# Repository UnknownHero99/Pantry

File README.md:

# Pantry

Self-hosted home inventory: pantry, fridge, freezer, garage, anything with a shelf.
Scan things **in** when you put them away and **out** when you use them, and always
know what you have.

- **Store-bought:** scan the product's own barcode (EAN/UPC). Name, brand and photo
  come from Open Food Facts, or for cleaners, toilet paper and toiletries from its
  sister databases Open Products Facts and Open Beauty Facts. Slovenian names come
  from [Veš, kaj ješ?](https://veskajjes.si) (ZPS), which is asked at the same time
  and also covers products Open Food Facts doesn't know. Packs of the same
  product are counted together.
- **Home-made** (harvest, bulk meat, meal prep): *Pack & label* prints one QR label per
  package on a Bluetooth cat printer. Each package keeps its own weight, packed date
  and use-by date, and scanning it OUT removes that exact package.
- **Wall scanner:** ESP32-P4 4.3" touchscreen (Guition) + GM67 barcode module, ESPHome firmware
  (`esphome/`). TAKE OUT / PUT AWAY modes, product photo, count before → after,
  −/+ for multiples, QR to name unknown barcodes, offline queue, ambient night clock.
- **Phone PWA:** camera scanning, inventory, shopping list, inbox for unknown barcodes,
  history with undo. Pages still open offline, and offline scans are queued and replayed.
- **Home Assistant:** shopping list mirrored to a to-do list; `/api/summary` for sensors.

Stack: SvelteKit (adapter-node) + SQLite (`node:sqlite`, no native deps), one container.

## Screenshots

The wall scanner: waiting for a scan, a product taken out, a home-made package taken out.

The phone app: Pantry stock, the Garage, one box, the shopping list, packing and labelling home-made food.

## Run

```bash
cp .env.example .env     # set ORIGIN, optionally HA_*
docker compose pull && docker compose up -d
docker logs pantry       # the one-time setup code
```

Open the app, enter the setup code from the log and create the admin account. Then, in
**More → Users & devices**, add the rest of the household and make a device token for the
wall scanner (and one for Home Assistant).

Every push to `master` builds `ghcr.io/unknownhero99/pantry:latest` (amd64 + arm64) in GitHub Actions. To run your own checkout instead, use `docker compose up -d --build`.

Data (SQLite DB + cached product photos) lives in `./data` → `/data` in the container.

Dev: `npm install && npm run dev` (port 5190, data in `./data`).

### Environment

| Var | |
|---|---|
| `ORIGIN` | Public HTTPS URL behind your reverse proxy, e.g. `https://pantry.example.com`. SvelteKit form posts check it. |
| `DATA_DIR` | Defaults to `/data` in the image. |
| `TZ` | Time zone for History, e.g. `Europe/Ljubljana` (the default in `docker-compose.yml`). |
| `HA_URL`, `HA_TOKEN`, `HA_TODO_ENTITY` | Optional grocery-list sync, e.g. `http://192.168.10.10:20810`, a long-lived token, `todo.shopping_list`. |
| `HA_TODO_ENTITY_GARAGE` | Optional: the garage shopping list into its own HA to-do list, e.g. `todo.hardware_store`. |
| `HA_NOTIFY` | Optional: "Lent to…" reminders as phone notifications, e.g. `notify.mobile_app_pixel_8`. |
| `TRUSTED_PROXIES` | Optional: comma-separated addresses of your reverse proxy. Only they may set `X-Forwarded-For` / `-Proto` / `-Host`. Unset, any private or loopback address is trusted (a proxy on the LAN or in Docker). |

### Reverse proxy

The phone needs **HTTPS** for the camera, PWA install and Web Bluetooth. Proxy to port
5190. `/api/events` is a server-sent-events stream, so turn off response buffering for
it (nginx: `proxy_buffering off;`; the app also sends `X-Accel-Buffering: no`).

The wall scanner talks plain HTTP straight to `http://<nas>:5190`, not through the proxy.

The proxy must pass `X-Forwarded-For` and `X-Forwarded-Proto` (Caddy, Traefik and Nginx Proxy
Manager do by default; plain nginx needs `proxy_set_header X-Forwarded-For
$proxy_add_x_forwarded_for;` and `proxy_set_header X-Forwarded-Proto $scheme;`). Pantry uses them
to rate-limit sign-in per client and to mark the session cookie `Secure`. HSTS belongs on the proxy.

## Sign-in and security

Everything except the sign-in page needs an account; nothing is readable without one.

- **People** sign in with a username and password (6+ characters, scrypt-hashed). The browser
  gets a random session cookie (`HttpOnly`, `SameSite=Lax`, `Secure` over HTTPS) that lasts 30
  days from the last visit, so phones stay signed in. The database stores only a hash of it.
  **More → Account** changes your password (which signs out your other devices), lists where
  you're signed in and signs any of them out.
- **Admins** also get **More → Users & devices**: add people, set a new password for someone,
  make them admin, remove them. There's always at least one admin.
- **Devices** (the wall scanner, Home Assistant) use a token from Users & devices, sent as
  `Authorization: Bearer pnt_…`. A token opens `/api/*` and `/img/*`, never the pages, is shown
  once, stored hashed, and can be revoked there at any time.
- **First run:** with no accounts, every page goes to `/setup`, which asks for a one-time code
  printed in the server log, so whoever reaches a fresh install first can't claim it.
- **Brute force:** after 10 failed sign-ins from one address, or 20 for one username, in 15
  minutes, sign-in is refused for the rest of that window. Failures are logged with the
  client's address.
- **Cross-site requests:** every POST from a browser must come from this site (its `Origin`
  is checked against the request's host, `ORIGIN`, or the proxy's `X-Forwarded-Host`). Pages
  send a Content-Security-Policy (scripts only from the app), `X-Frame-Options: DENY`,
  `nosniff` and `Referrer-Policy: same-origin`.

Locked out? Remove the users and Pantry asks for setup again (stock is untouched):

```bash
docker exec pantry node -e "new (require('node:sqlite').DatabaseSync)('/data/pantry.db').exec('DELETE FROM users')"
docker restart pantry && docker logs pantry
```

## Spaces: Pantry, Kitchen, Garage

Storage is a small tree: **spaces** › **places** › **boxes**.

| Space | Places (at first) | Lists |
|---|---|---|
| **Pantry**, the home space | Shelves, Freezer | Groceries, *Use soon*. The wall scanner files here. |
| **Kitchen** | Fridge, Freezer | Groceries, *Use soon* (same lists as Pantry) |
| **Garage** | Unsorted (+ your shelves) | its own Garage shopping list |

- The **Stock** tab opens on Pantry; tap the title (*Pantry ▾*) to switch space.
  Search always looks **everywhere** and answers with the path,
  e.g. *Garage › Shelf A › A·1 Power tools*.
- Add spaces and places in **Settings → Spaces and places**. A space shops into either
  Groceries or the Garage list.
- **Boxes:** on a shelf's page, *+ New numbered boxes* makes A·1, A·2… and prints their
  labels on the P15 (QR `PNTRY:B:…`). Scanning a box label on the phone opens the box;
  *Move box* moves everything inside with it.
- **Sorting the garage:** open a box, *+ Put in*: snap a photo, name it, *Tool / Spare part
  / Other*, what a spare part **fits**, *Just 1* or *Count them*. *Save, next thing*.
  Not sure where something goes? Put it in *Unsorted* and move it later.
- **Counted** things (bulbs, filters, screws) have a quantity and a minimum, like food.
  **Located** things (a drill) only have a place: *Took it* / *Put back*, *Move…*,
  and *Lent to…* with a reminder (7 / 14 / 30 days) through Home Assistant.
- Migrating from before spaces: the old Pantry becomes *Pantry › Shelves*, Freezer
  *Pantry › Freezer*, Fridge *Kitchen › Fridge*; nothing else changes.

See `docs/storage-design.md` for the reasoning.

## Using it

The phone app looks and talks like the wall: dark, TAKE OUT / PUT AWAY, the same result
card. Tabs: Stock · Shop · **Scan** (the big middle button) · Pack · More.

| Screen | |
|---|---|
| **Stock** | Tiles for *to buy*, *use soon*, *to name*; search; filter by place; tap a count for −/+ |
| **Shop** | Groceries and Garage lists: below *min stock*, with photos. Ticks ("in the trolley") stay on your phone; *Put away* opens Scan in put-away mode |
| **Scan** | Camera (+ torch, + type a code), TAKE OUT / PUT AWAY (falls back after 2 min, like the wall), result card with −/+, undo, fix count, the trip list |
| **Pack** | Home-made goods: recent products as chips, packs × amount, where, use-by chips, live label preview → print |
| **Product** | Count per place, packages, details. An unknown barcode (the wall's QR code lands here) opens as a quick *name it* form |
| **More → Inbox** | Barcodes neither Open Food Facts nor Veš kaj ješ knew |
| **More → History** | By day, filter wall / phones / count issues, undo any of them |
| **More → Settings** | Locations, printer darkness + test print |

Set **Min stock** on a product to have it appear on the shopping list.
**Keeps (days)** pre-fills use-by when packing. It's learned from the first pack if blank.

### Label printers

Printing happens **from the phone over Web Bluetooth**: Chrome on Android, over HTTPS.
On the first print, Chrome lists nearby Bluetooth devices; pick the printer. The app
recognises which kind it is and draws the label for it. Choose the kind in **Settings** so
previews match before you've connected. Close the printer's own app first: these printers
take one connection at a time.

| | **P15** label maker (Marklife / Pristar P15, P12, L13) | **C15** "cat" printer (Fun Print) |
|---|---|---|
| Labels | 12–15 mm die-cut labels, 30 / 40 / 50 mm long (set in Settings) | 57 mm thermal sticker roll |
| Layout | QR across the full 12 mm height, name / amount / dates beside it | QR left, larger text right |
| Driver | `src/lib/p15printer.js`: service `0xFF00`, ESC/POS raster (`GS v 0`) in a `10 FF …` job | `src/lib/catprinter.js`: the `51 78 …` protocol (MX/GB models) |
| Darkness | fixed | slider in Settings |

The P15 job format follows what the [LaBLEr](https://github.com/toolicious/labler) project
verified on a P15 (our bytes match its reference job exactly). If a printer isn't
recognised, the error lists the Bluetooth services it does offer. Stick labels on dry bags
*before* freezing.

Labels encode `PNTRY:I:000123`. The wall scanner and phone camera both read them.

## Wall scanner (`esphome/`)

### Parts

Everything is off the shelf; no custom board needed. Prices are delivered to Slovenia
with VAT and the EU's per-item import charges (about €6.10 an item from China, November
2026). [hardware/shopping-list.md](hardware/shopping-list.md) has the listings and says
which parts to buy locally instead, because the charge is several times their price.

| | |
|---|---|
| Guition **JC4880P443C** (ESP32-P4 + ESP32-C6 for Wi-Fi, 4.3" 480×800 IPS used in landscape, GT911 capacitive touch) | ~€38 |
| **GROW GM67** barcode module (1D + 2D, red aiming light, 5 V, TTL UART; comes with its cables). The [enclosure](hardware/enclosure) is made for it; a GM65 or the SparkFun breakout works with the same firmware. | ~€25 |
| **Speaker**, 8 Ω 1–2 W, round 28 mm × 5 mm, with a 1.25 mm 2-pin plug on a lead of 15 cm or more: it plugs into the board's own amplifier | ~€10 |
| **WS2812B LED module**, a single LED (DIN, VCC, GND) | ~€1 |
| Three female Dupont wires, a **right-angle** USB-C cable and a 5 V 2 A supply | ~€15 |
| [3D-printed case](hardware/enclosure) (or any wall box) | |

The speaker and LED are optional. Without the speaker, the GM67's own beep confirms each
read (leave its silent mode off), and the firmware can stay as it is: the sounds just play
to nothing. Without both, drop the `feedback` package and the speaker section from
`pantry-scanner.yaml`.

### Wiring

| Guition | Goes to |
|---|---|
| The 1.25 mm 4-pin socket marked **5V, IO26, IO27, GND**: `5V` | GM67 UART pin 1 `5V` |
| `IO26` (the board's RX) | GM67 pin 2 `TX` |
| `IO27` (the board's TX) | GM67 pin 3 `RX` |
| `GND` | GM67 pin 4 `GND` |
| **Speaker socket** (1.25 mm 2-pin, on the board's top edge) | speaker |
| **JP1** (2×13 header) pins **2, 4, 6**: 3.3 V, GND, GPIO33 | LED VCC, GND, DIN |

Pin for pin, so the GM67's own 4-pin UART cable plugs straight in. The GM67's UART socket
is the one marked UART, next to the USB one. Not **CN2 "UART0"**: on this board it's
GPIO21/GPIO38, and a GM67 on it never got through.

The LED takes three neighbouring header pins, so it's one 3-pin Dupont plug and no
splicing. It runs on 3.3 V so its data input sees a full-level signal; WS2812B LEDs are
rated from 3.5 V but work at 3.3 V. The speaker is driven by the board's ES8311 audio chip
and amplifier (enabled on GPIO11); the scan sounds are the same tunes a buzzer would play.

Flashing and logs go over the USB-C marked **full speed** (the ESP32-P4's USB
Serial/JTAG), so the scanner can stay plugged in.

**Other boards.** [esphome/pantry-sunton.yaml](esphome/pantry-sunton.yaml) is the same
thing on the Sunton **ESP32-8048S043C** (ESP32-S3, ~€52 delivered), with its wiring in the
file's header. Two optional custom boards, neither needed:
[hardware/scanner-carrier](hardware/scanner-carrier) sits behind the Sunton with sockets for
the scanner, a buzzer and a status LED; [hardware/mainboard](hardware/mainboard) replaces it
with one 4-layer board for the bare panel ([esphome/pantry-mainboard.yaml](esphome/pantry-mainboard.yaml)).

### Scanner module setup

Using the configuration barcodes in the scanner's manual (the
[GM67 manual](https://makerselectronics.com/wp-content/uploads/2026/07/GM67-Barcode-Reader-Module-User-Manual-V1.3.pdf)):
**serial (UART) output, 9600 baud, induction/continuous mode, add CR suffix**, and make
sure QR codes are enabled. The GM67 also beeps by itself on every read; its **silent mode**
leaves the beeping to the speaker, which sounds different for each result. With no
speaker, leave silent mode off.
(Or keep its baud rate and change `scanner_baud` in `pantry-scanner.yaml`.)

### Flash

```bash
cd esphome
cp secrets.example.yaml secrets.yaml   # Wi-Fi, API key: openssl rand -base64 32 (OTA uses it too)
# edit substitutions at the top of pantry-scanner.yaml: server URL, location name
docker run --rm -it -v "$PWD":/config --device /dev/ttyACM0 esphome/esphome run pantry-scanner.yaml
```

The first flash prints the chip's revision (`Chip is ESP32-P4 (revision v…)`). Below
v3.0 it's an early chip: set `engineering_sample: "true"` in `pantry-scanner.yaml` and
flash again. After that, update over Wi-Fi.

Or use the ESPHome dashboard in Home Assistant: copy `pantry-scanner.yaml`,
`pantry-ui.yaml` (the screens), `pantry-feedback.yaml` (LED and scan sounds) and `pantry_ui.h`
into its config folder. The board shows up in HA with a backlight light
and a "Last scan" sensor, and takes its clock from HA, so it needs no internet.

**Wi-Fi co-processor.** The P4 has no radio; Wi-Fi is the ESP32-C6 beside it. These boards
ship with an older C6 firmware than ESPHome expects, which can drop Wi-Fi now and then.
Once the scanner is in HA, install the **Wi-Fi co-processor** update it offers (ESPHome's
build, downloaded by the scanner itself).

Make a device token in the app (**More → Users & devices → New token**, e.g. "Wall
scanner") and put it in `secrets.yaml` as `pantry_token`; the scanner sends it with every
request. Without it, or after it's revoked, the server answers 401 and the scanner can't
scan, so make the token before flashing.

Set `ORIGIN` on the server: the unknown-barcode screen shows a QR code of
`<ORIGIN>/product/<id>`, which opens the product on your phone to name it.

The config is validated and compiles against ESPHome 2026.10 (RAM 16%, flash 24%), but
hasn't run on a board yet. The display and Wi-Fi settings are ESPHome's own for this board
(`model: JC4880P443`, ESP-Hosted over SDIO) and the pins come from its schematic notes.
If the picture is upside down, set `rotation: "270"`. Touch is polled, because the
sources disagree on its reset and interrupt pins.

### Try it without the hardware

`pantry-sim.yaml` runs the same screens in an 800×480 window on a Linux desktop (X11).
The mouse is the touchscreen, and a small script stands in for the barcode module.
It talks to the app on `http://127.0.0.1:5190`, so start that first (`npm run dev`).

Put a device token from the app in `token:` at the top of `pantry-sim.yaml` first.

```bash
esphome/sim/run.sh                   # builds a Docker image with SDL, compiles, opens the window
esphome/sim/scan 3017620422003       # "scan" a barcode (Nutella); PNTRY:I:000001 for a label
```

The first build takes a few minutes. Set `ORIGIN` in `.env` to see the QR code on
the unknown-barcode screen. The backlight does nothing in the window, so the night screen
shows at full brightness.

**Network:** if the scanner lives on the IoT VLAN, the router needs an allow rule from
it to the NAS on TCP 5190.

### On the wall

The screen has a status bar on top (clock, or a blue "PUTTING AWAY" band), a card in the
middle, and a fixed bottom bar: **TAKE OUT | PUT AWAY** and **UNDO**.

- **Take out** is the default. Scan anything you take: the card shows the photo,
  **3 → 2 left**, and goes back to the home screen (what to buy, what to use soon,
  items to name) after 8 seconds. Took two? Tap **+**.
- **Put away** before unpacking shopping. The top bar turns blue and counts down; after
  2 minutes without a scan it falls back to take out. Each scan shows **2 → 3** and lands
  in the *This trip* list. Bought six of the same? Scan one, tap **+** five times.
- **First time a barcode is seen:** "Looking it up…" while the server asks Open Food
  Facts in the background. If it isn't found, the screen shows a **QR code**: point
  your phone at it to name the product right away, or do it later from the inbox.
- **Took the last one:** an amber banner says so, and whether it's on the shopping list
  (set *Min stock* on the product for that).
- **Home-made package:** packed date, use-by, what's left, and a hint if an older pack
  should be used first.
- **Nothing in stock** (counts drifted): *It was there, fix count* records the one the
  app didn't know about.
- **UNDO** opens a list of this scanner's last 5 scans from the past day, newest on top.
  Tap the one to reverse (any −/+ on it is reversed too); **CLOSE** or 20 s without a
  tap closes the list.
- **Server unreachable:** keep scanning. Scans wait on the scanner and are sent when the
  server is back (kept in RAM, so a power cut loses them).
- After 5 minutes without a touch or scan it shows a dim clock with what to buy and use
  soon; a touch or scan wakes it.

## Home Assistant

Shopping list: set the `HA_*` variables. The app adds and removes only the items it put
there, so items you add by hand are left alone.

Sensors from `/api/summary`, with a device token (Users & devices → New token, e.g. "Home
Assistant") in HA's `secrets.yaml` as `pantry_auth: "Bearer pnt_…"`:

```yaml
rest:
  - resource: http://192.168.10.10:5190/api/summary
    headers:
      Authorization: !secret pantry_auth
    scan_interval: 300
    sensor:
      - name: Pantry low stock
        value_template: "{{ value_json.low_count }}"
        json_attributes: [low]
      - name: Pantry use soon
        value_template: "{{ value_json.expiring_count }}"
        json_attributes: [expiring]
      - name: Pantry inbox
        value_template: "{{ value_json.inbox_count }}"
```

## API

Every call needs either a signed-in browser session or `Authorization: Bearer <device token>`;
without one the answer is `401`.

| | |
|---|---|
| `POST /api/scan` `{code, mode: "in"\|"out", device?, location?, default_location?, async_lookup?}` — `location` forces a place, `default_location` only applies to products without a usual place, `async_lookup` answers at once and looks a new barcode up in the background | → `{status: ok\|lookup\|unknown\|empty\|error, title, detail, count, prev, units, meta, image, qr, last_one, pkg, use_by, older, product_id, event_id, …}` (see `scanReply` in `inventory.js`) |
| `GET /api/scan/:event` | The same reply for an earlier scan; the wall polls it while `status` is `lookup` |
| `POST /api/scan/:event/adjust` `{by: 1\|-1}` | One more or one fewer of that scan ("bought six") |
| `POST /api/scan/:event/fix` | For a nothing-in-stock OUT: record that there was one |
| `GET /api/scan/recent?device=wall` | That device's last 5 scans from the past day that can still be undone (the wall's UNDO list) |
| `POST /api/undo` `{event_id?}` | Undo that event, or the latest one |
| `GET /api/summary` | `{low_count, low[], expiring_count, expiring[], soon[{name, n, days}], inbox_count, garage_low_count, lent_out, overdue[]}` (`low` is groceries) |
| `GET /api/labels?ids=1,2` | Label data for reprinting |
| `GET /api/events` | SSE stream: `change` whenever stock moves |

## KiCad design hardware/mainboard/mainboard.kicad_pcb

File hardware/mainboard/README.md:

# Wall scanner mainboard

Everything for the wall scanner on one board: it replaces the Sunton ESP32-8048S043C.
A 100 × 60 mm, 4-layer board that sits behind a bare 4.3" 800×480 RGB panel; every part
is on the back, so JLCPCB assembles one side only. Optional: an off-the-shelf display
board plus modules does the same job (see the [main README](../../README.md#wall-scanner-esphome)).
Goes into the [printable enclosure](../enclosure) built with `board = "mainboard"`
(`stl/mainboard-*.stl`).

- **ESP32-S3-WROOM-1-N16R8** (16 MB flash, 8 MB PSRAM), antenna over the top edge.
- **USB-C** is the ESP32-S3's native USB: power, flashing and logs. ESD protected (USBLC6),
  works with USB-C chargers (5.1 k CC pull-downs).
- **3.3 V**: SY8089 buck, 2 A.
- **Display**: 40-pin 0.5 mm ribbon (Hirose FH12, bottom contact), 16-bit RGB like the
  Sunton. The ESP32-S3 can put these signals on any GPIO, so they're assigned in the order
  they meet the module's edge seen from the connector: the 20 display lines reach it
  without crossing (with the Sunton's pin order they'd cross about 90 times).
  **Backlight**: TPS61169 constant-current boost (about 20 mA, 37.5 V limit), PWM from IO5.
- **Touch**: GT911 on a 6-pin 1.0 mm ribbon; IO39 SDA, IO40 SCL, IO41 INT, IO42 RST.
- **Scanner** on UART0 (IO43/44), which is free because flashing goes over USB:
  - **J4**: SparkFun 2D Barcode Scanner Breakout (DE2120, red aiming line), 3.3 V, on a
    1×6 socket. In the [enclosure](../enclosure) it sits in the bevelled mouth under the
    screen and connects with a short 6-wire Dupont cable; without the enclosure a
    right-angle header plugs it straight in.
  - **J5**: any 5 V UART module (GM65, GM805, GM861…) on a 4-pin 1.25 mm cable instead.
  Fit only one.
- **Buzzer** MLT-8530 (IO2) and a **status LED**: side-view SK6812 on the bottom edge
  shining down (IO1, level-shifted to 5 V).
- **RESET** and **BOOT** buttons (rarely needed: USB flashing doesn't need them).

## Files

| | |
|---|---|
| `fab/mainboard-gerbers.zip` | Gerbers + drill files for JLCPCB: **4 layers**, 1.6 mm |
| `fab/bom-jlcpcb.csv`, `fab/cpl-jlcpcb.csv` | Parts and placement for JLCPCB assembly (LCSC numbers, in stock Oct 2026) |
| `fab/mainboard-schematic.pdf` | Schematic |
| `fab/mainboard.step` | 3D model |
| `mainboard.kicad_*` | KiCad 10 project |

## Ordering (JLCPCB)

1. Upload the Gerber zip, choose **4 layers** (the inner two are a ground and a 3.3 V plane).
2. PCB Assembly, top side, upload the BOM and CPL.
3. Check the placement preview, especially U2/U4 (SOT-23-5), U5 (SC-70-5), the two ribbon
   connectors, D3 (side LED, light toward the bottom edge) and LS1 (`+` top left).
4. J4 (1×6 socket) is through-hole: let JLCPCB fit it or solder it.

## Panel

Any 4.3" 800×480 RGB TFT with the common 40-pin pinout (LED−, LED+, GND, VDD, R0–R7,
G0–G7, B0–B7, GND, DCLK, DISP, HSYNC, VSYNC, DE, NC, GND, 4 × resistive touch) and a
GT911 capacitive touch on a separate 6-pin 1.0 mm ribbon (GND, SDA, SCL, RST, INT, VDD):
the panel the Sunton boards use. Both ribbons wrap around the board's bottom edge into
the connectors on the back.

## Firmware

[esphome/pantry-mainboard.yaml](../../esphome/pantry-mainboard.yaml): the same screens
(`pantry-ui.yaml`) and the buzzer / LED package (`pantry-feedback.yaml`) as the
Sunton build with the carrier, on this board's pins (the display block lists this board's
RGB GPIOs; the panel timing is unchanged). Flash it over USB-C the first time, over Wi-Fi
after that.

## Rebuilding

Everything comes from [tools/design.py](tools/design.py):

```bash
hardware/mainboard/tools/build.sh
```

Same steps as the [scanner carrier](../scanner-carrier#rebuilding), with a bigger router:
the USB-C escape (a fixed pattern in `design.py`: D+ joins on top, D- through two vias)
and the USB nets first, then a via for every ground and 3.3 V pad into the inner planes,
then everything else by negotiated congestion (PathFinder): nets may overlap at first, at
a price that rises each round, until none do. The strips behind the ribbon connectors are
left to the ground pour, which picks up their fine-pitch ground pins. About 10 minutes.

## Not verified yet

Nothing has been built. KiCad's checks are clean (see the build log), but:

- **The panel ribbon's contact side and pin 1 end** are the part most likely to be wrong for
  a given panel. Both connectors are bottom-contact (the ribbon's contacts face the board
  after it wraps around the edge) and have **pin 1 at the left end seen from the back of
  the board** (the right end seen from the front). Check your panel's drawing: its ribbon
  must arrive that way round, or the connectors need turning in `tools/design.py`.
- **Backlight current**: R13 = 10 Ω gives about 20 mA. Some panels want 40 mA (two strings):
  then use 5.1 Ω.
- The side LED's footprint is drawn from its datasheet (KiCad doesn't have it).

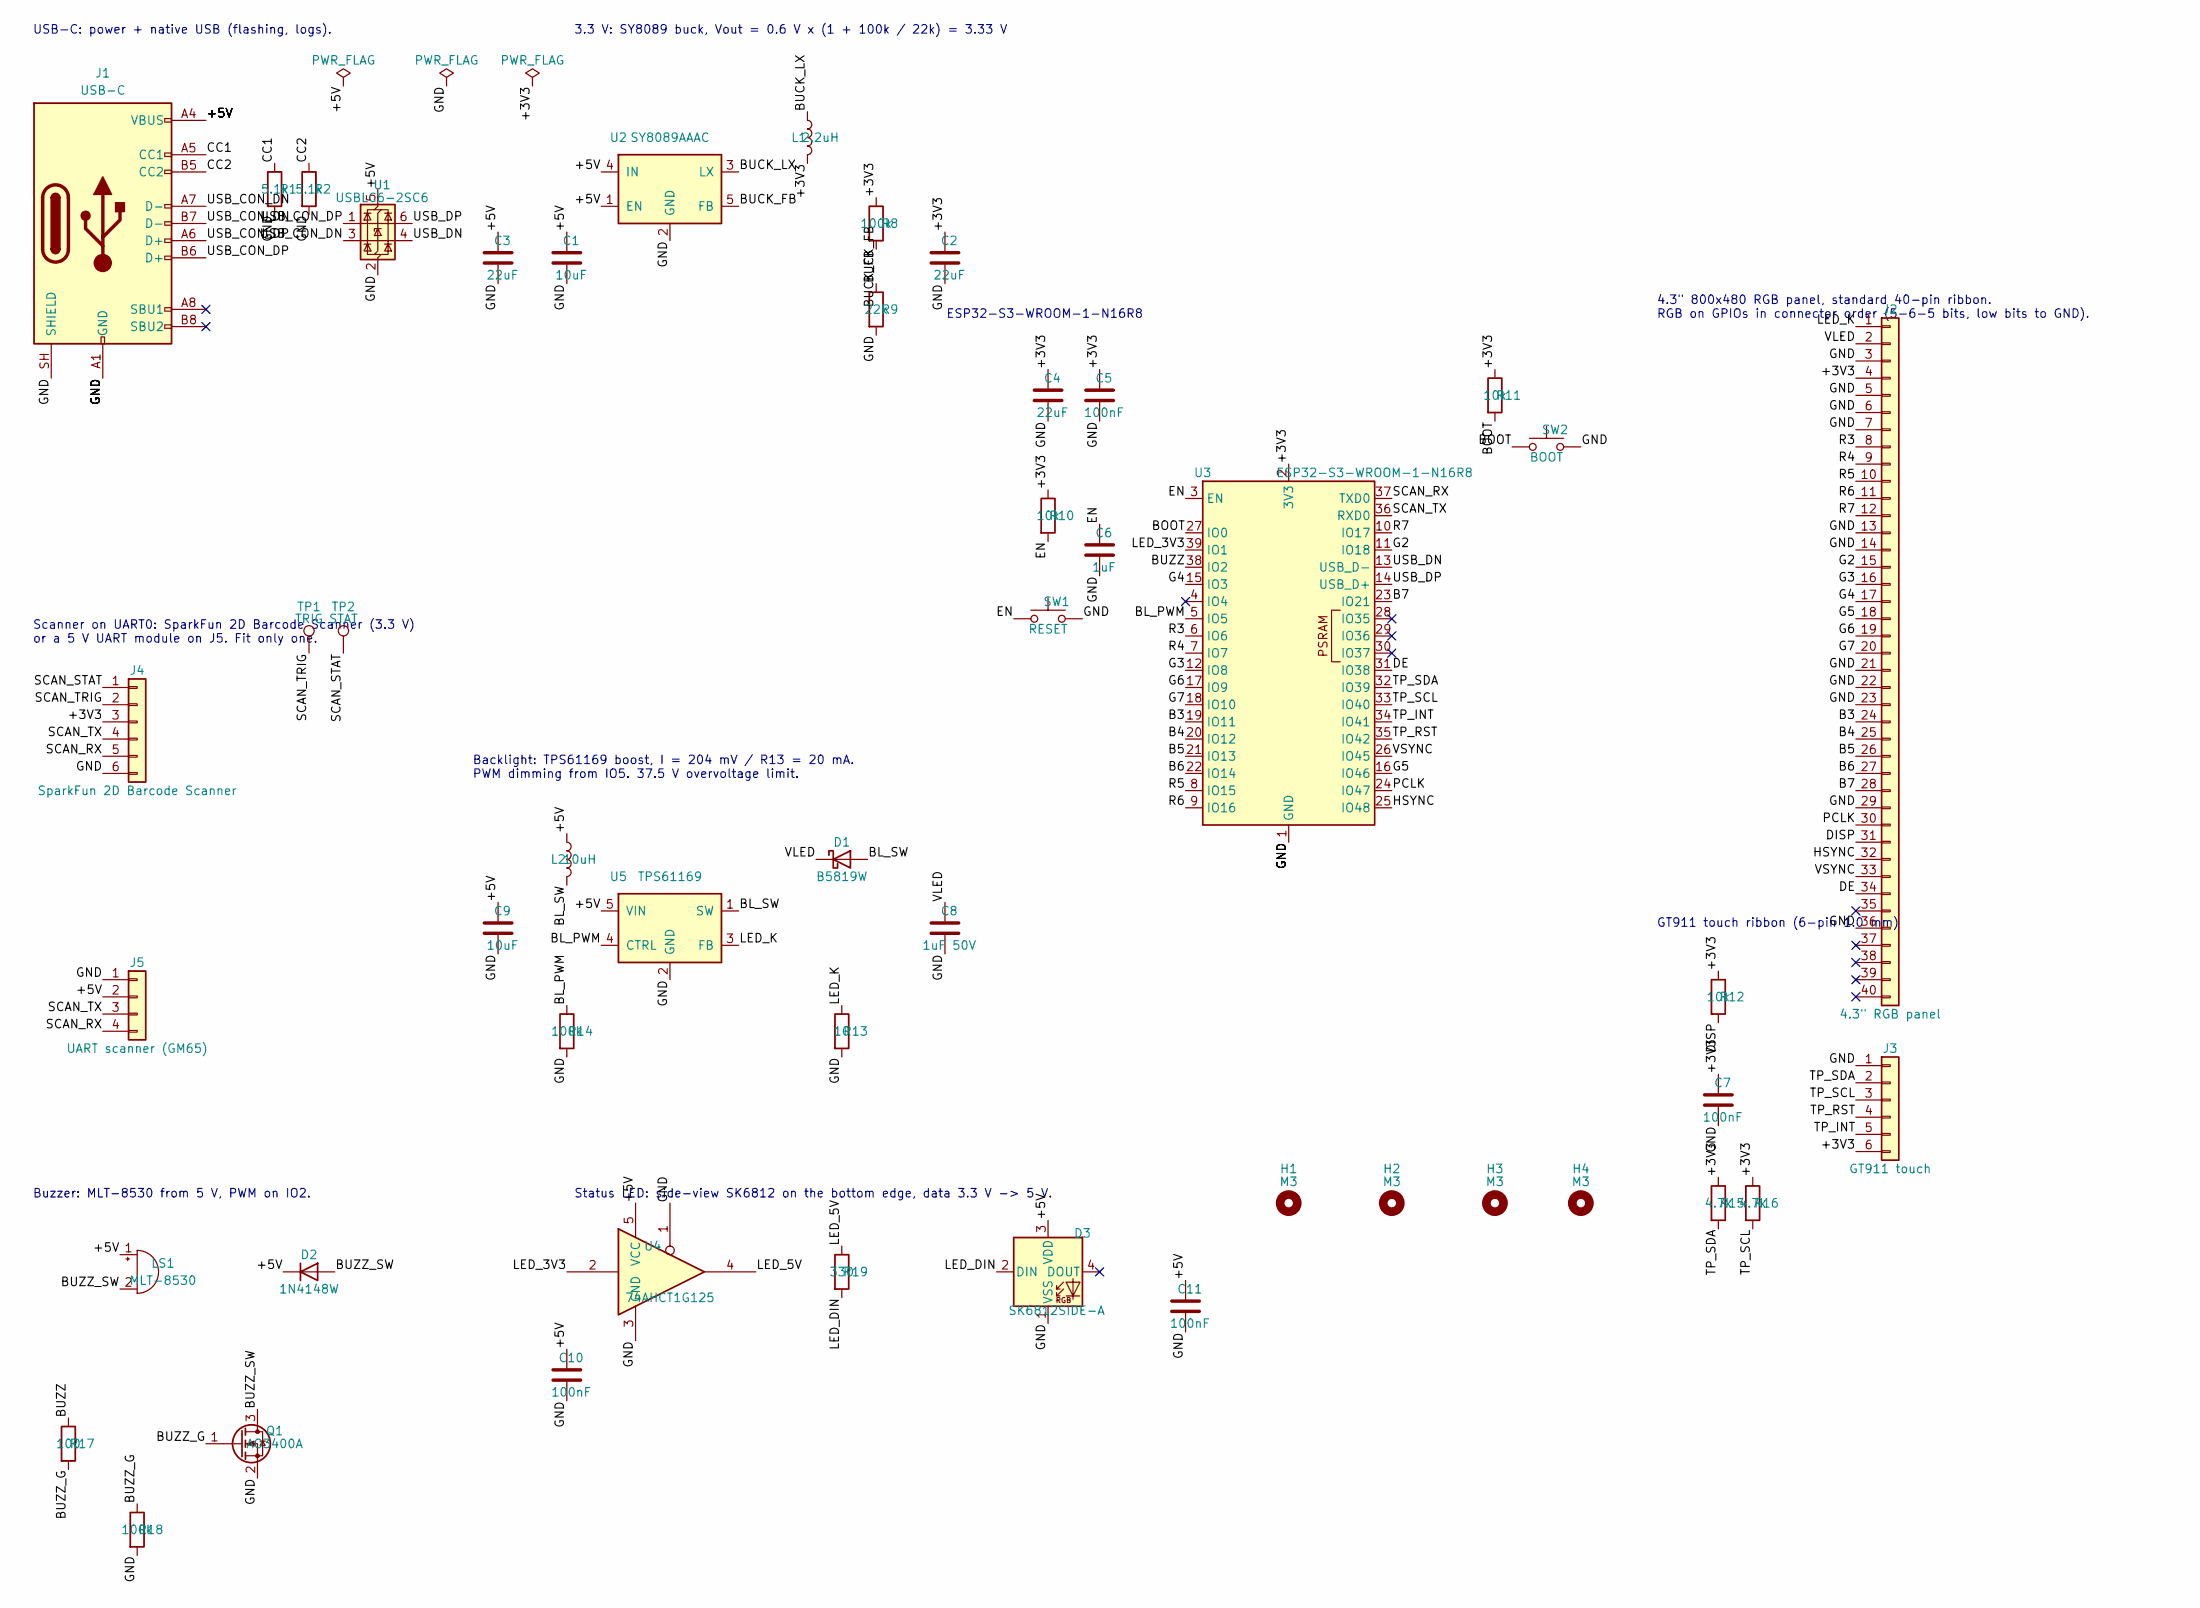
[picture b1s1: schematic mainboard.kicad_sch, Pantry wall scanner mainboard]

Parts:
C1, C9: 10uF; C_0805_2012Metric; LCSC C15850
C2, C3, C4: 22uF; C_0805_2012Metric; LCSC C45783
C5, C7, C10, C11: 100nF; C_0603_1608Metric; LCSC C14663
C6: 1uF; C_0603_1608Metric; LCSC C15849
C8: 1uF 50V; C_0805_2012Metric; LCSC C28323
D1: B5819W; D_SOD-123; LCSC C8598
D2: 1N4148W; D_SOD-123; LCSC C81598
D3: SK6812SIDE-A; LED_SK6812SIDE-A_4.0x1.6mm; LCSC C5378721
H1, H2, H3, H4: M3; MountingHole_3.2mm_M3
J1: USB-C; USB_C_Receptacle_HRO_TYPE-C-31-M-12; LCSC C165948
J2: 4.3" RGB panel; Hirose_FH12-40S-0.5SH_1x40-1MP_P0.50mm_Horizontal; LCSC C202114
J3: GT911 touch; JUSHUO_AFA07-S06FCA-00_1x6-1MP_P1.0mm_Horizontal; LCSC C262712
J4: SparkFun 2D Barcode Scanner; PinSocket_1x06_P2.54mm_Vertical; LCSC C40877
J5: UART scanner (GM65); Molex_PicoBlade_53261-0471_1x04-1MP_P1.25mm_Horizontal; LCSC C696092
L1: 2.2uH; L_Taiyo-Yuden_NR-40xx; LCSC C92959
L2: 10uH; L_Taiyo-Yuden_NR-40xx; LCSC C222882
LS1: MLT-8530; Buzzer_MLT-8530; LCSC C94599
Q1: AO3400A; SOT-23; LCSC C20917
R1, R2: 5.1k; R_0603_1608Metric; LCSC C23186
R8, R14, R18: 100k; R_0603_1608Metric; LCSC C25803
R9: 22k; R_0603_1608Metric; LCSC C31850
R10, R11, R12: 10k; R_0603_1608Metric; LCSC C25804
R13: 10; R_0603_1608Metric; LCSC C22859
R15, R16: 4.7k; R_0603_1608Metric; LCSC C23162
R17: 100; R_0603_1608Metric; LCSC C22775
R19: 330; R_0603_1608Metric; LCSC C23138
SW1: RESET; SW_Push_1P1T_XKB_TS-1187A; LCSC C318884
SW2: BOOT; SW_Push_1P1T_XKB_TS-1187A; LCSC C318884
TP1: TRIG; TestPoint_Pad_D1.0mm
TP2: STAT; TestPoint_Pad_D1.0mm
U1: USBLC6-2SC6; SOT-23-6; LCSC C7519
U2: SY8089AAAC; SOT-23-5; LCSC C78988
U3: ESP32-S3-WROOM-1-N16R8; ESP32-S3-WROOM-1; LCSC C2913202
U4: 74AHCT1G125; SOT-23-5; LCSC C7484
U5: TPS61169; SOT-353_SC-70-5; LCSC C71045

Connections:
/+3V3: C2.1, C4.1, C5.1, C7.1, J2.4, J3.6, J4.3, L1.2, R8.1, R10.1, R11.1, R12.1, R15.1, R16.1, U3.2 (3V3)
/+5V: C1.1, C3.1, C9.1, C10.1, C11.1, D2.1 (K), D3.3 (VDD), J1.A4 (VBUS), J1.A9 (VBUS), J1.B4 (VBUS), J1.B9 (VBUS), J5.2, L2.1, LS1.1 (+), U1.5 (VBUS), U2.1 (EN), U2.4 (IN), U4.5 (VCC), U5.5 (VIN)
/B3: J2.24, U3.19 (IO11)
/B4: J2.25, U3.20 (IO12)
/B5: J2.26, U3.21 (IO13)
/B6: J2.27, U3.22 (IO14)
/B7: J2.28, U3.23 (IO21)
/BL_PWM: R14.1, U3.5 (IO5), U5.4 (CTRL)
/BL_SW: D1.2 (A), L2.2, U5.1 (SW)
/BOOT: R11.2, SW2.1, U3.27 (IO0)
/BUCK_FB: R8.2, R9.1, U2.5 (FB)
/BUCK_LX: L1.1, U2.3 (LX)
/BUZZ: R17.1, U3.38 (IO2)
/BUZZ_G: Q1.1 (G), R17.2, R18.1
/BUZZ_SW: D2.2 (A), LS1.2 (-), Q1.3 (D)
/CC1: J1.A5 (CC1), R1.1
/CC2: J1.B5 (CC2), R2.1
/DE: J2.34, U3.31 (IO38)
/DISP: J2.31, R12.2
/EN: C6.1, R10.2, SW1.1, U3.3 (EN)
/G2: J2.15, U3.11 (IO18)
/G3: J2.16, U3.12 (IO8)
/G4: J2.17, U3.15 (IO3)
/G5: J2.18, U3.16 (IO46)
/G6: J2.19, U3.17 (IO9)
/G7: J2.20, U3.18 (IO10)
/GND: C1.2, C2.2, C3.2, C4.2, C5.2, C6.2, C7.2, C8.2, C9.2, C10.2, C11.2, D3.1 (VSS), J1.A1 (GND), J1.A12 (GND), J1.B1 (GND), J1.B12 (GND), J1.SH (SHIELD), J2.3, J2.5, J2.6, J2.7, J2.13, J2.14, J2.21, J2.22, J2.23, J2.29, J2.36, J3.1, J4.6, J5.1, Q1.2 (S), R1.2, R2.2, R9.2, R13.2, R14.2, R18.2, SW1.2, SW2.2, U1.2 (GND), U2.2 (GND), U3.1 (GND), U3.40 (GND), U3.41 (GND), U4.1, U4.3 (GND), U5.2 (GND)
/HSYNC: J2.32, U3.25 (IO48)
/LED_3V3: U3.39 (IO1), U4.2
/LED_5V: R19.1, U4.4
/LED_DIN: D3.2 (DIN), R19.2
/LED_K: J2.1, R13.1, U5.3 (FB)
/PCLK: J2.30, U3.24 (IO47)
/R3: J2.8, U3.6 (IO6)
/R4: J2.9, U3.7 (IO7)
/R5: J2.10, U3.8 (IO15)
/R6: J2.11, U3.9 (IO16)
/R7: J2.12, U3.10 (IO17)
/SCAN_RX: J4.5, J5.4, U3.37 (TXD0)
/SCAN_STAT: J4.1, TP2.1
/SCAN_TRIG: J4.2, TP1.1
/SCAN_TX: J4.4, J5.3, U3.36 (RXD0)
/TP_INT: J3.5, U3.34 (IO41)
/TP_RST: J3.4, U3.35 (IO42)
/TP_SCL: J3.3, R16.2, U3.33 (IO40)
/TP_SDA: J3.2, R15.2, U3.32 (IO39)
/USB_CON_DN: J1.A7 (D-), J1.B7 (D-), U1.3 (I/O2)
/USB_CON_DP: J1.A6 (D+), J1.B6 (D+), U1.1 (I/O1)
/USB_DN: U1.4 (I/O2), U3.13 (USB_D-)
/USB_DP: U1.6 (I/O1), U3.14 (USB_D+)
/VLED: C8.1, D1.1 (K), J2.2
/VSYNC: J2.33, U3.26 (IO45)

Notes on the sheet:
USB-C: power + native USB (flashing, logs).
3.3 V: SY8089 buck, Vout = 0.6 V x (1 + 100k / 22k) = 3.33 V
ESP32-S3-WROOM-1-N16R8
4.3" 800x480 RGB panel, standard 40-pin ribbon. RGB on GPIOs in connector order (5-6-5 bits, low bits to GND).
Backlight: TPS61169 boost, I = 204 mV / R13 = 20 mA. PWM dimming from IO5. 37.5 V overvoltage limit.
GT911 touch ribbon (6-pin 1.0 mm)
Scanner on UART0: SparkFun 2D Barcode Scanner (3.3 V) or a 5 V UART module on J5. Fit only one.
Buzzer: MLT-8530 from 5 V, PWM on IO2.
Status LED: side-view SK6812 on the bottom edge, data 3.3 V -> 5 V.

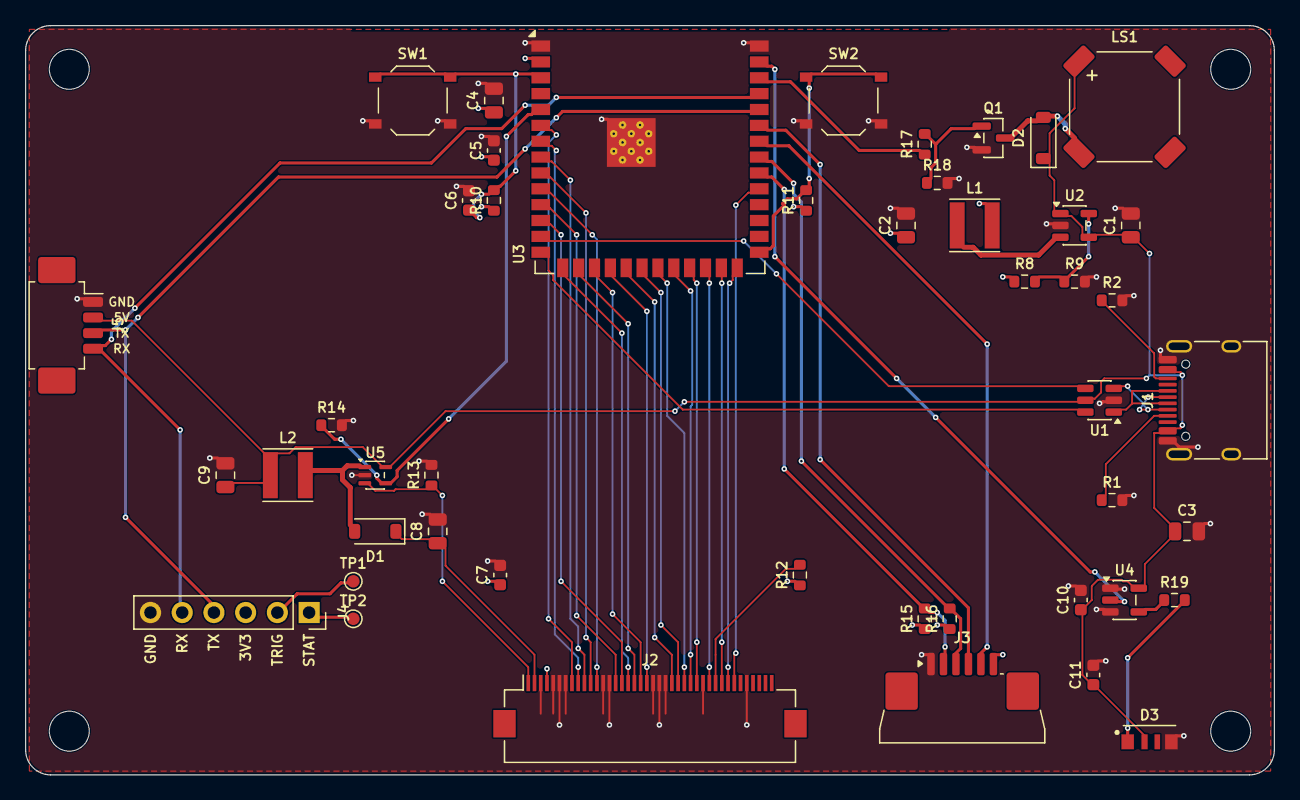
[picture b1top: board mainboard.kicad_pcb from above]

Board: 4 copper layers, 100.0 x 60.0 mm, 50 parts (0 on the bottom side), 52 nets.

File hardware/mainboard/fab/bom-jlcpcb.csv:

Comment,Designator,Footprint,LCSC Part #
10uF,"C1,C9",C_0805_2012Metric,C15850
22uF,"C2,C3,C4",C_0805_2012Metric,C45783
100nF,"C5,C7,C10,C11",C_0603_1608Metric,C14663
1uF,C6,C_0603_1608Metric,C15849
1uF 50V,C8,C_0805_2012Metric,C28323
B5819W,D1,D_SOD-123,C8598
1N4148W,D2,D_SOD-123,C81598
SK6812SIDE-A,D3,LED_SK6812SIDE-A_4.0x1.6mm,C5378721
USB-C,J1,USB_C_Receptacle_HRO_TYPE-C-31-M-12,C165948
"4.3"" RGB panel",J2,Hirose_FH12-40S-0.5SH_1x40-1MP_P0.50mm_Horizontal,C202114
GT911 touch,J3,JUSHUO_AFA07-S06FCA-00_1x6-1MP_P1.0mm_Horizontal,C262712
SparkFun 2D Barcode Scanner,J4,PinSocket_1x06_P2.54mm_Vertical,C40877
Molex PicoBlade 53261-0471 1x4 right-angle,J5,Molex_PicoBlade_53261-0471_1x04-1MP_P1.25mm_Horizontal,C696092
2.2uH,L1,L_Taiyo-Yuden_NR-40xx,C92959
10uH,L2,L_Taiyo-Yuden_NR-40xx,C222882
MLT-8530,LS1,Buzzer_MLT-8530,C94599
AO3400A,Q1,SOT-23,C20917
5.1k,"R1,R2",R_0603_1608Metric,C23186
10k,"R10,R11,R12",R_0603_1608Metric,C25804
10,R13,R_0603_1608Metric,C22859
4.7k,"R15,R16",R_0603_1608Metric,C23162
100,R17,R_0603_1608Metric,C22775
330,R19,R_0603_1608Metric,C23138
100k,"R8,R14,R18",R_0603_1608Metric,C25803
22k,R9,R_0603_1608Metric,C31850
RESET,SW1,SW_Push_1P1T_XKB_TS-1187A,C318884
BOOT,SW2,SW_Push_1P1T_XKB_TS-1187A,C318884
USBLC6-2SC6,U1,SOT-23-6,C7519
SY8089AAAC,U2,SOT-23-5,C78988
ESP32-S3-WROOM-1-N16R8,U3,ESP32-S3-WROOM-1,C2913202
74AHCT1G125,U4,SOT-23-5,C7484
TPS61169,U5,SOT-353_SC-70-5,C71045

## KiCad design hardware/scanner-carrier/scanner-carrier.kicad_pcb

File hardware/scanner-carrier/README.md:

# Scanner carrier board

A 64 × 44 mm two-layer board that sits behind the Sunton ESP32-8048S043C and
adds a scanner socket, a buzzer and a status LED. Optional: the same parts as
off-the-shelf modules wired straight to the Sunton need no board at all (see the
header of [pantry-sunton.yaml](../../esphome/pantry-sunton.yaml)); this is the tidier
version for a box of your own (the [printable enclosure](../enclosure) is laid out for
the modules):

- **SparkFun 2D Barcode Scanner Breakout** (DyScan DE2120): the red aiming line,
  reads EAN/UPC *and* the QR labels. It plugs into a 1×6 socket and an M3 standoff.
  A GM65/GM861 still fits on the 4-pin **GM65** socket instead (fit only one scanner).
- **Buzzer** (MLT-8530, driven from 5 V): beeps you can hear through a case.
- **Status LED** (WS2812B): green taken out, blue put away, amber new barcode, red problem.

Everything here is generated from [tools/design.py](tools/design.py), the one
place parts, nets and positions are written down. See [Rebuilding](#rebuilding).

## Files

| | |
|---|---|
| [fab/scanner-carrier-gerbers.zip](fab/scanner-carrier-gerbers.zip) | Gerbers + drill files: upload this to JLCPCB |
| [fab/bom-jlcpcb.csv](fab/bom-jlcpcb.csv), [fab/cpl-jlcpcb.csv](fab/cpl-jlcpcb.csv) | Parts list and placement for JLCPCB assembly (LCSC numbers, all in stock Oct 2026) |
| [fab/scanner-carrier-schematic.pdf](fab/scanner-carrier-schematic.pdf) | Schematic |
| [fab/scanner-carrier.step](fab/scanner-carrier.step) | 3D model, for designing the case |
| `scanner-carrier.kicad_pro` / `.kicad_sch` / `.kicad_pcb` | The KiCad 10 project, if you want to open or change it by hand |

## Ordering (JLCPCB)

1. Upload `fab/scanner-carrier-gerbers.zip`. Defaults are fine: 2 layers, 1.6 mm,
   HASL. The rules are inside JLCPCB's standard process: 0.25 mm tracks, 0.2 mm
   clearance, 0.3 mm vias.
2. Turn on **PCB Assembly**, top side, and upload `bom-jlcpcb.csv` and `cpl-jlcpcb.csv`.
3. **Check the placement preview.** KiCad and JLCPCB don't always agree on which
   way a part faces; the ones worth a look are U1 (SOT-223), U2 (SOT-23-5), D2 (the
   LED: its marked corner must land on the pad KiCad marks as pin 1), the three 1.25 mm
   sockets (openings toward the board edge) and LS1 (`+` corner top left). Rotate any that are off right there.
4. The 1×6 socket (J3) is through-hole: let JLCPCB fit it, or untick it and solder
   it yourself (a minute).

## Assembly

- **Scanner:** solder a straight 1×6 male header to the SparkFun board, pins down.
  It plugs into J3 with **GND on the left** (the SparkFun silkscreen matches the
  carrier's). One **M3 × 11 mm standoff** in H1 holds its far corner; the socket plus
  header make about 11 mm. (Its second hole sits too close to the header pins for a
  standoff to fit beside the socket, and the header holds that corner anyway.)
- **Case:** M3 holes H3/H4, plus the scanner standoff. The scanner, LED and buzzer
  all face away from the carrier, so mount it with that side toward the outside.

## Wiring to the Sunton

Two 4-pin 1.25 mm cables (the "MX1.25" ones that come with the Sunton boards):

| Carrier | Sunton | Carries |
|---|---|---|
| **J1 P1 UART** | P1 (GND, RX, TX, 5V) | power for the whole carrier, scanner UART |
| **J2 P4 IO** | P4 (IO18, IO17, 3V3, GND) | buzzer (IO18), status LED (IO17); the Sunton's 3.3 V is not used |

> **Before you power it up:** the carrier's pins are in the same order as the
> Sunton's silkscreen, assuming a straight 1:1 cable. Some MX1.25 cables are
> reversed. Check with a multimeter that Sunton GND reaches carrier GND on J1;
> a reversed J1 puts 5 V on ground.

Power is the Sunton's USB-C. The carrier adds up to roughly 0.4 A (the scanner most
of it), so use a 2 A supply.

## Firmware

In [esphome/pantry-sunton.yaml](../../esphome/pantry-sunton.yaml), replace the
`feedback` package (made for the modules) with the carrier's:

```yaml
packages:
  carrier: !include pantry-carrier.yaml
  ui: !include pantry-ui.yaml
```

[pantry-carrier.yaml](../../esphome/pantry-carrier.yaml) adds the buzzer (`rtttl`) and
the LED (`Status LED` in Home Assistant). The UI calls its `feedback` script after
every scan.

**Set up the DE2120** once with the configuration barcodes in its settings manual:
TTL/UART output, **9600 baud**, **CR suffix**, and a scan mode that suits you
(motion/continuous for a wall unit). Or leave its baud rate and change
`scanner_baud` in `pantry-sunton.yaml` to match.

## Rebuilding

Change [tools/design.py](tools/design.py) (or the scripts next to it), then:

```bash
hardware/scanner-carrier/tools/build.sh
```

It needs only Docker. In the `kicad/kicad:10.0.7-full` image it:
- writes the project rules ([make_pro.py](tools/make_pro.py));
- writes the schematic ([make_sch.py](tools/make_sch.py)) and runs ERC;
- places the footprints from the netlist ([make_pcb.py](tools/make_pcb.py));
- routes both layers with a small maze router ([route.py](tools/route.py));
- runs DRC with schematic parity;
- exports everything in `fab/` ([fab.py](tools/fab.py)).

The current board: **ERC 0, DRC 0 violations, 0 unconnected, 0 schematic mismatches.**

You can also open the project in KiCad and edit it there. After that, the
generator would overwrite your changes, so pick one way.

## Not verified yet

- Nothing has been built. The checks above are KiCad's; a first board is the real test.
- The **Sunton connector order** comes from the ESP3D documentation of this board,
  not from measuring one; check it and the cables (see above).
- The **MLT-8530 footprint** is drawn from the datasheet's outline (it gives no land
  pattern); JLCPCB's own footprint may differ slightly.
- The **DE2120's default baud rate**: set it as above rather than trusting a default.

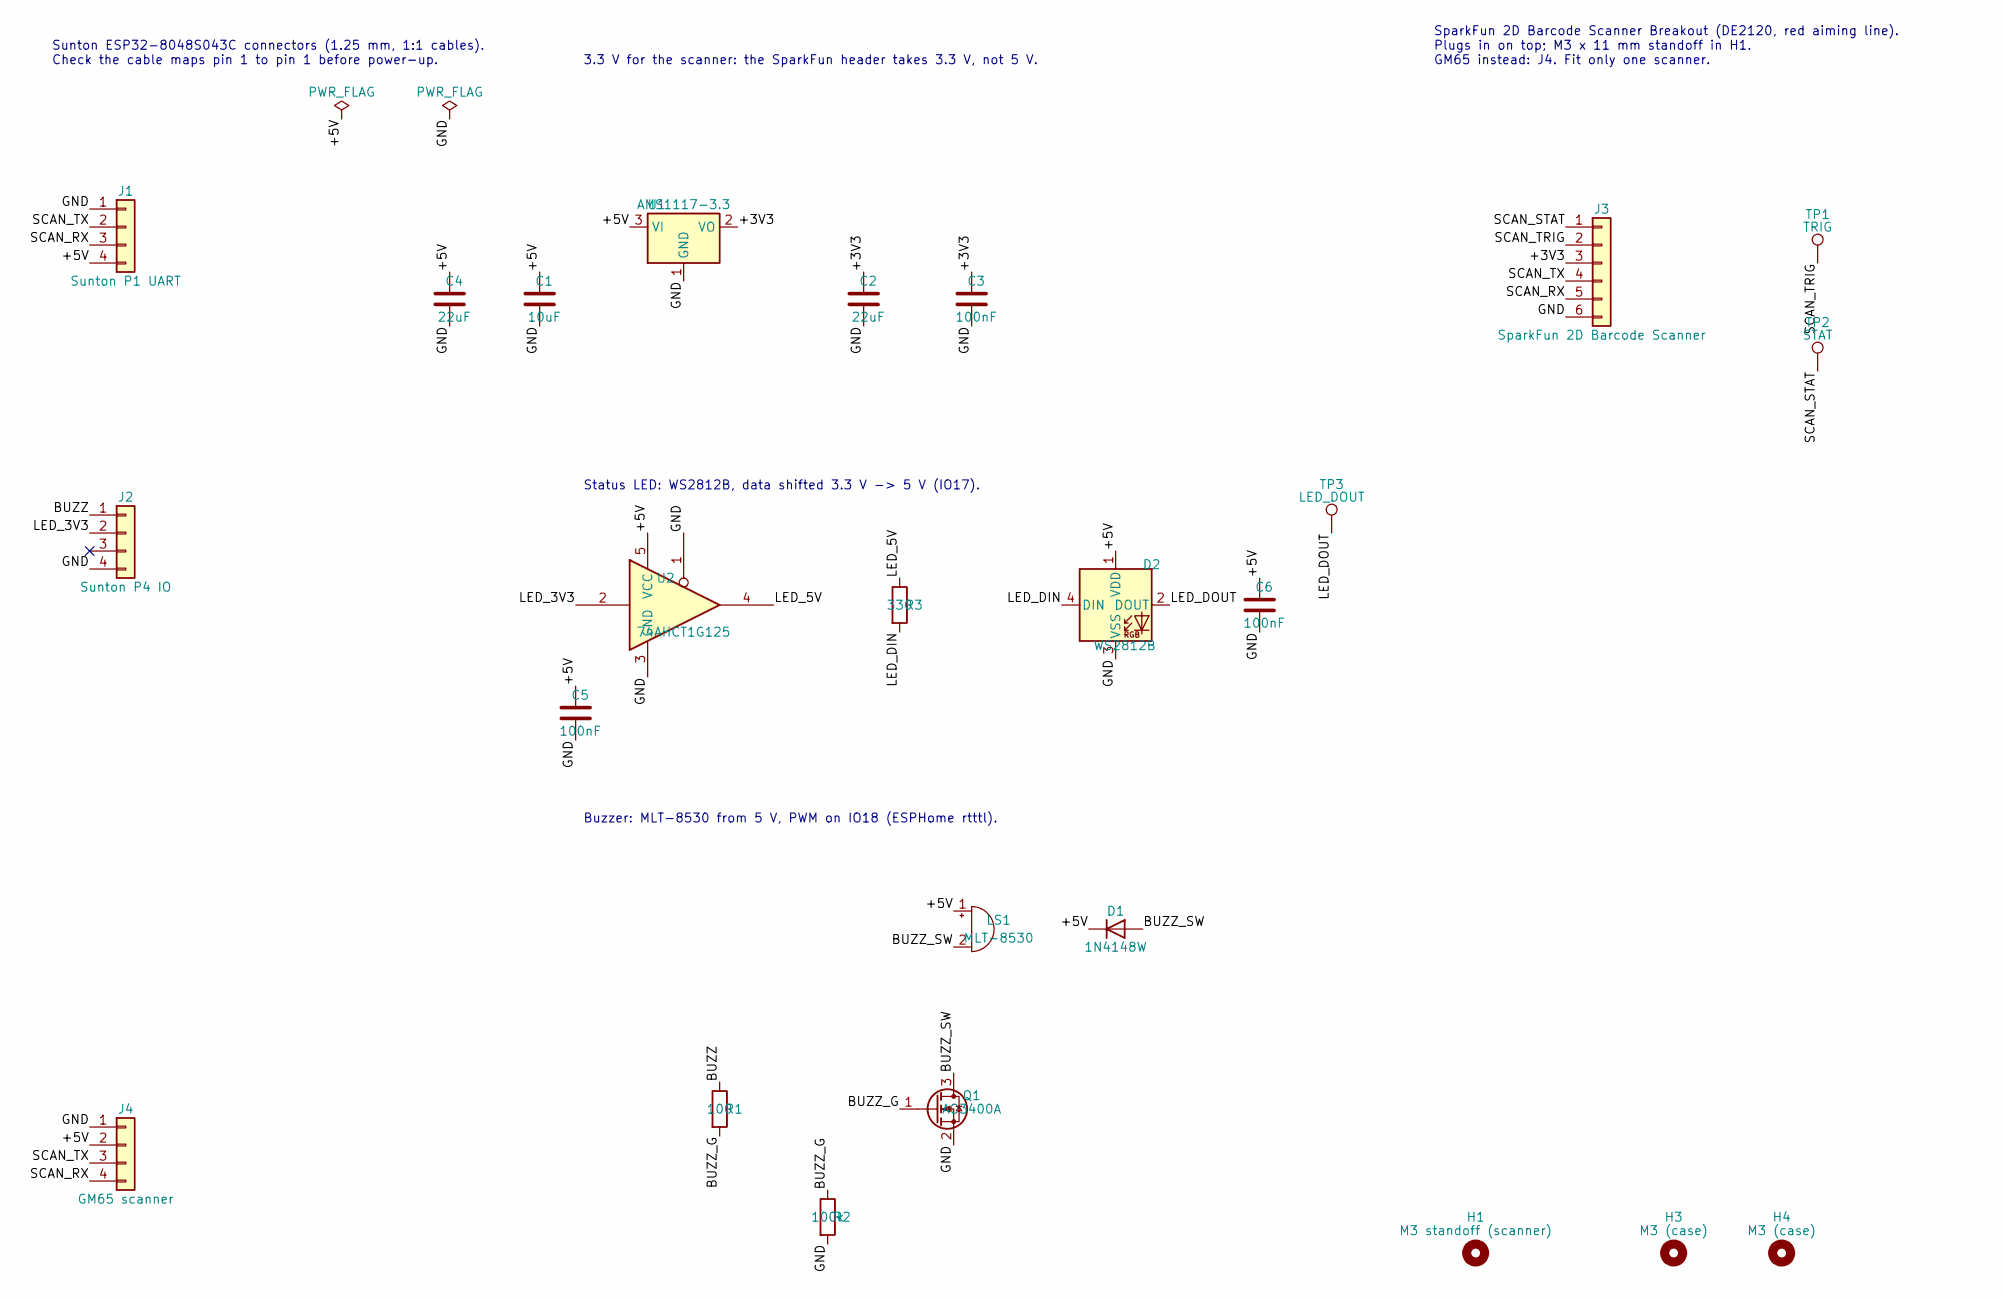
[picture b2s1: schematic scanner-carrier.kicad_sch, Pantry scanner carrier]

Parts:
C1: 10uF; C_0805_2012Metric; LCSC C15850
C2, C4: 22uF; C_0805_2012Metric; LCSC C45783
C3, C5, C6: 100nF; C_0603_1608Metric; LCSC C14663
D1: 1N4148W; D_SOD-123; LCSC C81598
D2: WS2812B; LED_WS2812B_PLCC4_5.0x5.0mm_P3.2mm; LCSC C2874885
H1: M3 standoff (scanner); MountingHole_3.2mm_M3
H3, H4: M3 (case); MountingHole_3.2mm_M3
J1: Sunton P1 UART; Molex_PicoBlade_53261-0471_1x04-1MP_P1.25mm_Horizontal; LCSC C696092
J2: Sunton P4 IO; Molex_PicoBlade_53261-0471_1x04-1MP_P1.25mm_Horizontal; LCSC C696092
J3: SparkFun 2D Barcode Scanner; PinSocket_1x06_P2.54mm_Vertical; LCSC C40877
J4: GM65 scanner; Molex_PicoBlade_53261-0471_1x04-1MP_P1.25mm_Horizontal; LCSC C696092
LS1: MLT-8530; Buzzer_MLT-8530; LCSC C94599
Q1: AO3400A; SOT-23; LCSC C20917
R1: 100; R_0603_1608Metric; LCSC C22775
R2: 100k; R_0603_1608Metric; LCSC C25803
R3: 330; R_0603_1608Metric; LCSC C23138
TP1: TRIG; TestPoint_Pad_D1.0mm
TP2: STAT; TestPoint_Pad_D1.0mm
TP3: LED_DOUT; TestPoint_Pad_D1.0mm
U1: AMS1117-3.3; SOT-223-3_TabPin2; LCSC C6186
U2: 74AHCT1G125; SOT-23-5; LCSC C7484

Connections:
/+3V3: C2.1, C3.1, J3.3, U1.2 (VO)
/+5V: C1.1, C4.1, C5.1, C6.1, D1.1 (K), D2.1 (VDD), J1.4, J4.2, LS1.1 (+), U1.3 (VI), U2.5 (VCC)
/BUZZ: J2.1, R1.1
/BUZZ_G: Q1.1 (G), R1.2, R2.1
/BUZZ_SW: D1.2 (A), LS1.2 (-), Q1.3 (D)
/GND: C1.2, C2.2, C3.2, C4.2, C5.2, C6.2, D2.3 (VSS), J1.1, J2.4, J3.6, J4.1, Q1.2 (S), R2.2, U1.1 (GND), U2.1, U2.3 (GND)
/LED_3V3: J2.2, U2.2
/LED_5V: R3.1, U2.4
/LED_DIN: D2.4 (DIN), R3.2
/LED_DOUT: D2.2 (DOUT), TP3.1
/SCAN_RX: J1.3, J3.5, J4.4
/SCAN_STAT: J3.1, TP2.1
/SCAN_TRIG: J3.2, TP1.1
/SCAN_TX: J1.2, J3.4, J4.3

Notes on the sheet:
Sunton ESP32-8048S043C connectors (1.25 mm, 1:1 cables). Check the cable maps pin 1 to pin 1 before power-up.
3.3 V for the scanner: the SparkFun header takes 3.3 V, not 5 V.
SparkFun 2D Barcode Scanner Breakout (DE2120, red aiming line). Plugs in on top; M3 x 11 mm standoff in H1. GM65 instead: J4. Fit only one scanner.
Status LED: WS2812B, data shifted 3.3 V -> 5 V (IO17).
Buzzer: MLT-8530 from 5 V, PWM on IO18 (ESPHome rtttl).

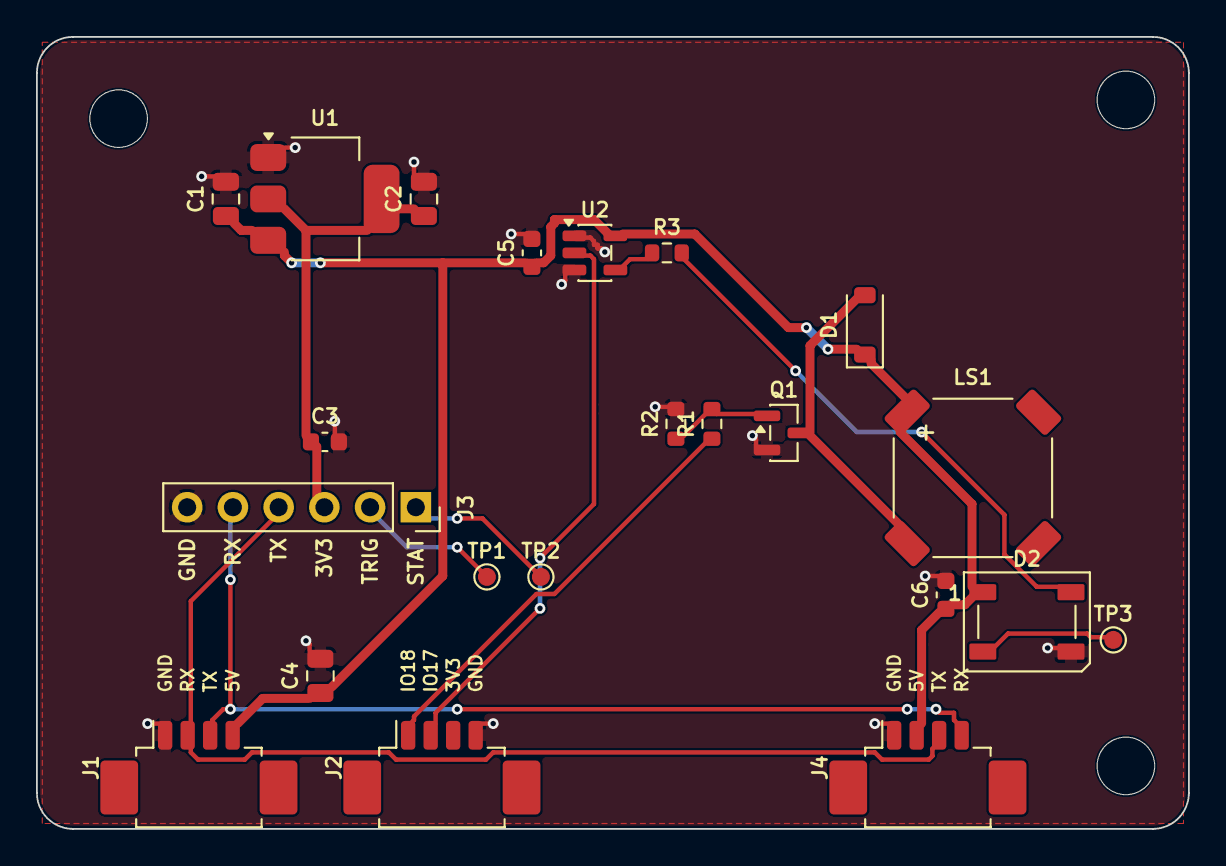
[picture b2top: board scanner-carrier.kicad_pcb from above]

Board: 2 copper layers, 64.0 x 44.0 mm, 25 parts (0 on the bottom side), 14 nets.

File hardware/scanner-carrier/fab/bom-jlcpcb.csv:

Comment,Designator,Footprint,LCSC Part #
10uF,C1,C_0805_2012Metric,C15850
22uF,"C2,C4",C_0805_2012Metric,C45783
100nF,"C3,C5,C6",C_0603_1608Metric,C14663
1N4148W,D1,D_SOD-123,C81598
WS2812B,D2,LED_WS2812B_PLCC4_5.0x5.0mm_P3.2mm,C2874885
Molex PicoBlade 53261-0471 1x4 right-angle,"J1,J2,J4",Molex_PicoBlade_53261-0471_1x04-1MP_P1.25mm_Horizontal,C696092
SparkFun 2D Barcode Scanner,J3,PinSocket_1x06_P2.54mm_Vertical,C40877
MLT-8530,LS1,Buzzer_MLT-8530,C94599
AO3400A,Q1,SOT-23,C20917
100,R1,R_0603_1608Metric,C22775
100k,R2,R_0603_1608Metric,C25803
330,R3,R_0603_1608Metric,C23138
AMS1117-3.3,U1,SOT-223-3_TabPin2,C6186
74AHCT1G125,U2,SOT-23-5,C7484
